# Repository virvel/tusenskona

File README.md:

# tusenskona

Breakout board for Daisy Seed

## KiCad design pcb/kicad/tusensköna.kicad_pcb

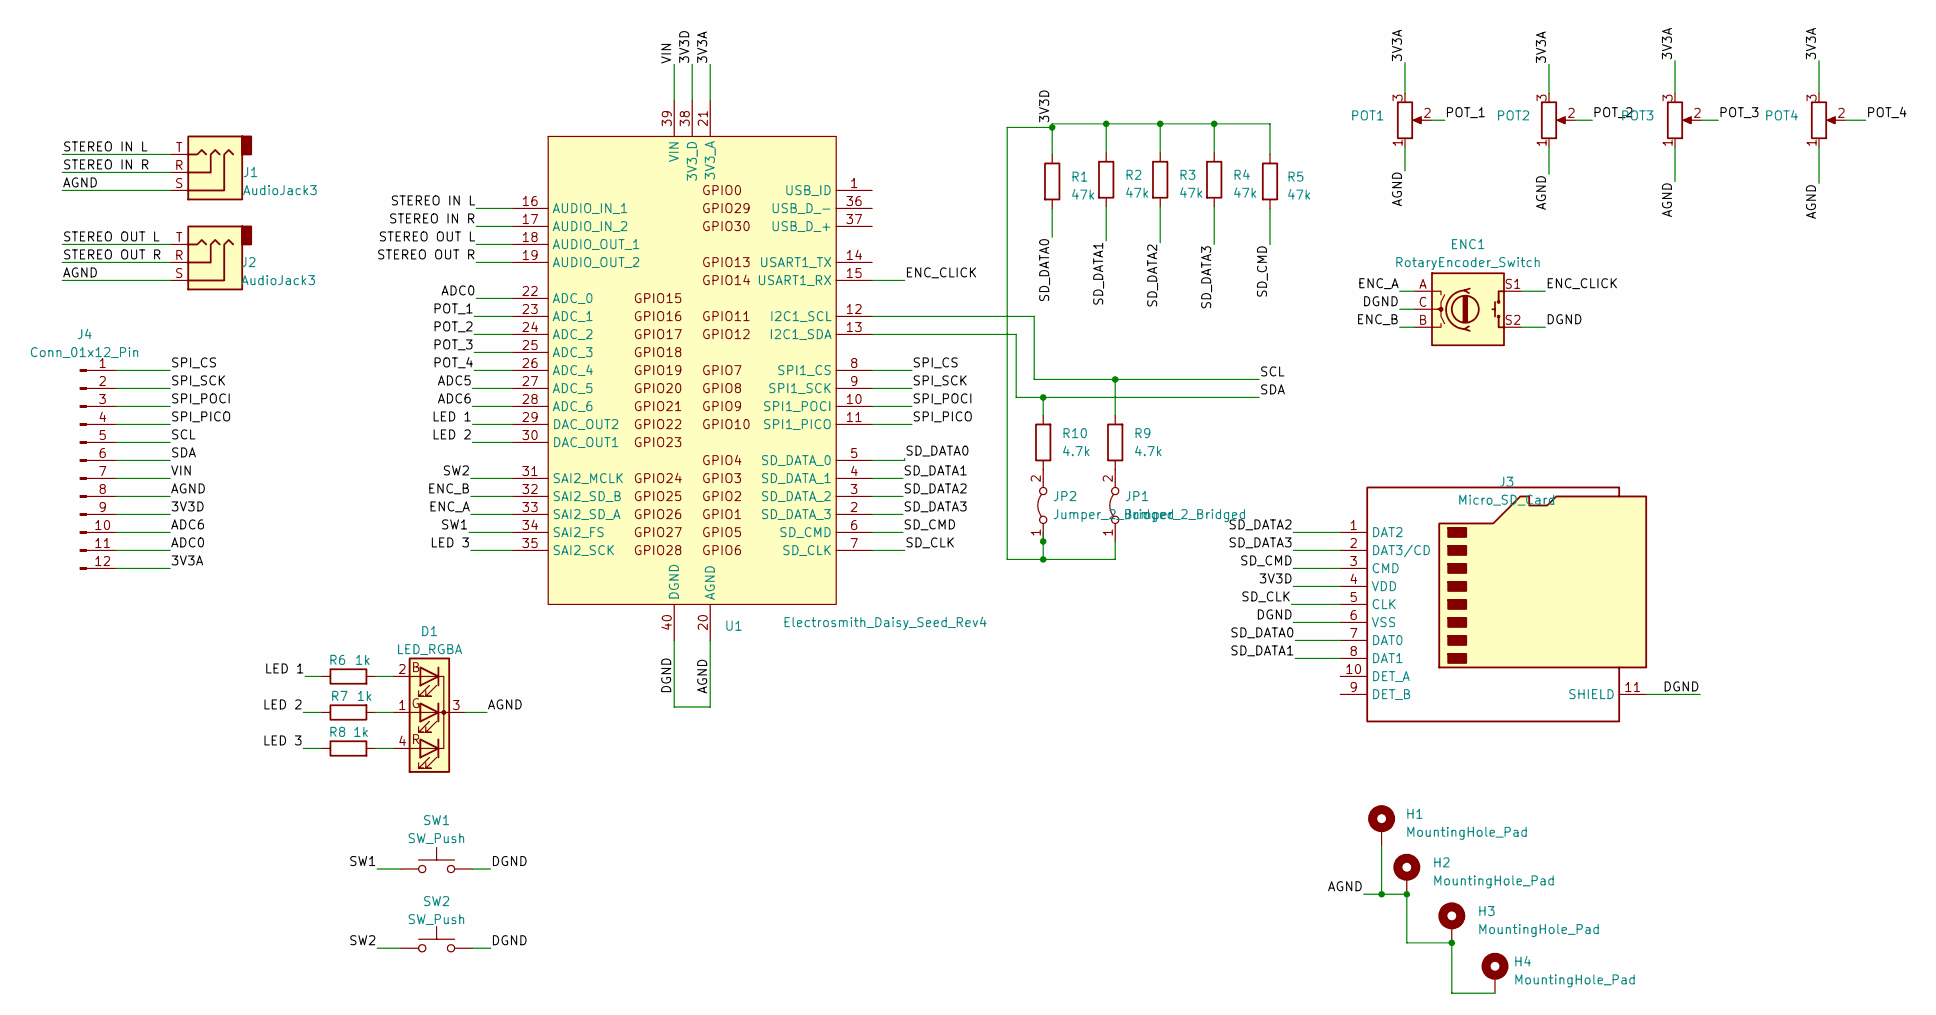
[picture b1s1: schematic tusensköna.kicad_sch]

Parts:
D1: LED_RGBA; LED_D5.0mm-4_RGB
ENC1: RotaryEncoder_Switch; RotaryEncoder_Bourns_Vertical_PEC12R-3xxxF-Sxxxx
H1, H2, H3, H4: MountingHole_Pad; MountingHole_3.2mm_M3_Pad
J1, J2: AudioJack3; Jack_3.5mm_CUI_SJ1-3533NG_Horizontal_CircularHoles
J3: Micro_SD_Card; microSD_HC_Hirose_DM3D-SF
J4: Conn_01x12_Pin; PinHeader_1x12_P2.54mm_Vertical
JP1, JP2: Jumper_2_Bridged; PinHeader_1x02_P2.54mm_Vertical
POT1, POT2, POT3, POT4: R_Potentiometer; Potentiometer_Alps_RK09K_Single_Vertical
R1, R2, R3, R4, R5: 47k; R_0805_2012Metric
R6, R7, R8: 1k; R_0805_2012Metric
R9, R10: 4.7k; R_0805_2012Metric
SW1, SW2: SW_Push; SW_PUSH_6mm
U1: Electrosmith_Daisy_Seed_Rev4; Electrosmith_Daisy_Seed

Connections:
/3V3A: J4.12, POT1.3, POT2.3, POT3.3, POT4.3, U1.21 (3V3_A)
/3V3D: J3.4 (VDD), J4.9, JP1.1 (A), JP2.1 (A), R1.1, R2.1, R3.1, R4.1, R5.1, U1.38 (3V3_D)
/ADC0: J4.11, U1.22 (ADC_0)
/ADC5: U1.27 (ADC_5)
/ADC6: J4.10, U1.28 (ADC_6)
/AGND: D1.3 (K), ENC1.C, ENC1.S2, H1.1, H2.1, H3.1, H4.1, J1.S, J2.S, J3.6 (VSS), J3.11 (SHIELD), J4.8, POT1.1, POT2.1, POT3.1, POT4.1, SW1.2, SW2.2, U1.20 (AGND), U1.40 (DGND)
/ENC_A: ENC1.A, U1.33 (SAI2_SD_A)
/ENC_B: ENC1.B, U1.32 (SAI2_SD_B)
/ENC_CLICK: ENC1.S1, U1.15 (USART1_RX)
/I2C_SCL: J4.5, R9.2, U1.12 (I2C1_SCL)
/I2C_SDA: J4.6, R10.2, U1.13 (I2C1_SDA)
/LED 1: R6.1, U1.29 (DAC_OUT2)
/LED 2: R7.1, U1.30 (DAC_OUT1)
/LED 3: R8.1, U1.35 (SAI2_SCK)
/POT_1: POT1.2, U1.23 (ADC_1)
/POT_2: POT2.2, U1.24 (ADC_2)
/POT_3: POT3.2, U1.25 (ADC_3)
/POT_4: POT4.2, U1.26 (ADC_4)
/SD_CLK: J3.5 (CLK), U1.7 (SD_CLK)
/SD_CMD: J3.3 (CMD), R5.2, U1.6 (SD_CMD)
/SD_DATA0: J3.7 (DAT0), R1.2, U1.5 (SD_DATA_0)
/SD_DATA1: J3.8 (DAT1), R2.2, U1.4 (SD_DATA_1)
/SD_DATA2: J3.1 (DAT2), R3.2, U1.3 (SD_DATA_2)
/SD_DATA3: J3.2 (DAT3/CD), R4.2, U1.2 (SD_DATA_3)
/SPI_CS: J4.1, U1.8 (SPI1_CS)
/SPI_PICO: J4.4, U1.11 (SPI1_PICO)
/SPI_POCI: J4.3, U1.10 (SPI1_POCI)
/SPI_SCK: J4.2, U1.9 (SPI1_SCK)
/STEREO IN L: J1.T, U1.16 (AUDIO_IN_1)
/STEREO IN R: J1.R, U1.17 (AUDIO_IN_2)
/STEREO OUT L: J2.T, U1.18 (AUDIO_OUT_1)
/STEREO OUT R: J2.R, U1.19 (AUDIO_OUT_2)
/SW1: SW1.1, U1.34 (SAI2_FS)
/SW2: SW2.1, U1.31 (SAI2_MCLK)
/VIN: J4.7, U1.39 (VIN)
unnamed: D1.2 (BA), R6.2
unnamed: D1.1 (GA), R7.2
unnamed: D1.4 (RA), R8.2
unnamed: JP1.2 (B), R9.1
unnamed: JP2.2 (B), R10.1

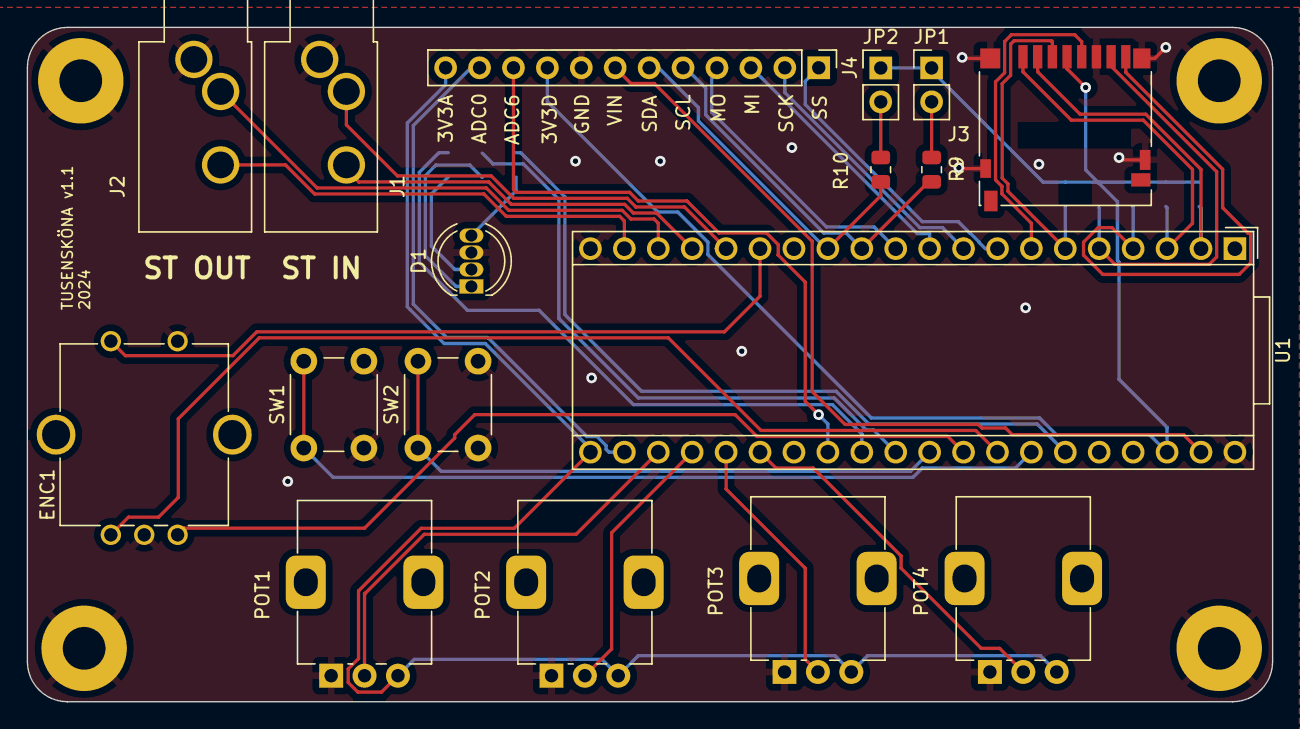
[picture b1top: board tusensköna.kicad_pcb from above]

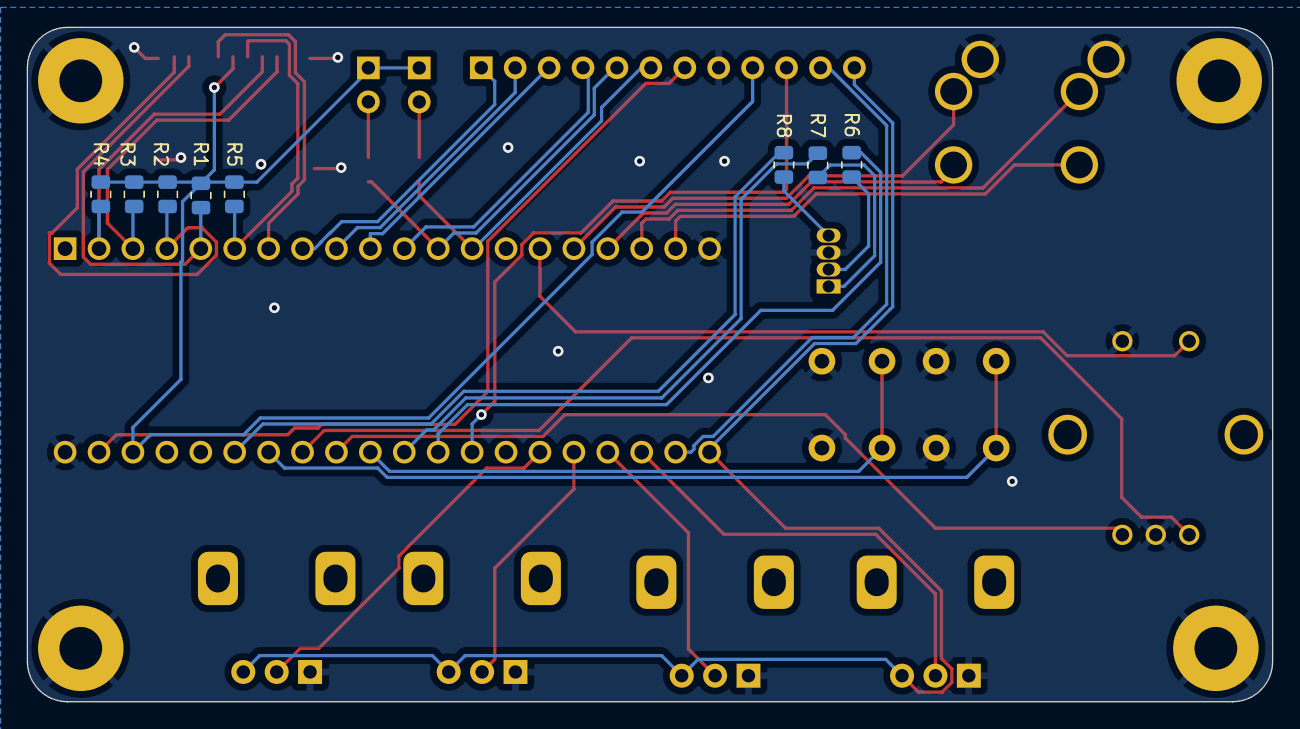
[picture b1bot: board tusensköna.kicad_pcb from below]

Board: 2 copper layers, 93.2 x 50.5 mm, 29 parts (8 on the bottom side), 39 nets.

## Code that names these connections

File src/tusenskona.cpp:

#include "tusenskona.h"

#ifndef SAMPLE_RATE
//#define SAMPLE_RATE DSY_AUDIO_SAMPLE_RATE
#define SAMPLE_RATE 48014.f
#endif


#define SW_1_PIN 27
#define SW_2_PIN 24

#define ENC_A_PIN 26
#define ENC_B_PIN 25
#define ENC_CLICK_PIN 14

#define LED_R_PIN 28
#define LED_G_PIN 23
#define LED_B_PIN 22

#define KNOB_1_PIN 16
#define KNOB_2_PIN 17
#define KNOB_3_PIN 18
#define KNOB_4_PIN 19

using namespace daisy;

void Tusenskona::Init(bool boost)
{
    seed.Configure();
    seed.Init(boost);
    InitButtons();
    InitEncoder();
    InitLeds();
    InitKnobs();
    SetAudioBlockSize(48);
}

void Tusenskona::DelayMs(size_t del)
{
    seed.DelayMs(del);
}


void Tusenskona::SetHidUpdateRates()
{
    for(int i = 0; i < KNOB_LAST; i++)
    {
        knobs[i]->SetSampleRate(AudioCallbackRate());
    }
}

void Tusenskona::StartAudio(AudioHandle::InterleavingAudioCallback cb)
{
    seed.StartAudio(cb);
}

void Tusenskona::StartAudio(AudioHandle::AudioCallback cb)
{
    seed.StartAudio(cb);
}

void Tusenskona::ChangeAudioCallback(AudioHandle::InterleavingAudioCallback cb)
{
    seed.ChangeAudioCallback(cb);
}

void Tusenskona::ChangeAudioCallback(AudioHandle::AudioCallback cb)
{
    seed.ChangeAudioCallback(cb);
}

void Tusenskona::StopAudio()
{
    seed.StopAudio();
}

void Tusenskona::SetAudioBlockSize(size_t size)
{
    seed.SetAudioBlockSize(size);
    SetHidUpdateRates();
}

size_t Tusenskona::AudioBlockSize()
{
    return seed.AudioBlockSize();
}

void Tusenskona::SetAudioSampleRate(SaiHandle::Config::SampleRate samplerate)
{
    seed.SetAudioSampleRate(samplerate);
    SetHidUpdateRates();
}

float Tusenskona::AudioSampleRate()
{
    return seed.AudioSampleRate();
}

float Tusenskona::AudioCallbackRate()
{
    return seed.AudioCallbackRate();
}

void Tusenskona::StartAdc()
{
    seed.adc.Start();
}

void Tusenskona::StopAdc()
{
    seed.adc.Stop();
}


void Tusenskona::ProcessAnalogControls()
{
    knob1.Process();
    knob2.Process();
    knob3.Process();
    knob4.Process();
}

float Tusenskona::GetKnobValue(Knob k)
{
    size_t idx;
    idx = k < KNOB_LAST ? k : KNOB_1;
    return knobs[idx]->Value();
}

void Tusenskona::ProcessDigitalControls()
{
    encoder.Debounce();
    button1.Debounce();
    button2.Debounce();
}

void Tusenskona::ClearLeds()
{
    led.Set(0.0f, 0.0f, 0.0f);
}

void Tusenskona::UpdateLeds()
{
    led.Update();
}

void Tusenskona::InitButtons()
{
    // button1
    button1.Init(seed.GetPin(SW_1_PIN));
    // button2
    button2.Init(seed.GetPin(SW_2_PIN));

    buttons[BUTTON_1] = &button1;
    buttons[BUTTON_2] = &button2;
}

void Tusenskona::InitEncoder()
{
    dsy_gpio_pin a, b, click;
    a     = seed.GetPin(ENC_A_PIN);
    b     = seed.GetPin(ENC_B_PIN);
    click = seed.GetPin(ENC_CLICK_PIN);
    encoder.Init(a, b, click);
}

void Tusenskona::InitLeds()
{
    dsy_gpio_pin rpin, gpin, bpin;

    rpin = seed.GetPin(LED_R_PIN);
    gpin = seed.GetPin(LED_G_PIN);
    bpin = seed.GetPin(LED_B_PIN);
    led.Init(rpin, gpin, bpin, false);

    ClearLeds();
    UpdateLeds();
}
void Tusenskona::InitKnobs()
{
    // Configure the ADC channels using the desired pin
    AdcChannelConfig knob_init[KNOB_LAST];
    knob_init[KNOB_1].InitSingle(seed.GetPin(KNOB_1_PIN));
    knob_init[KNOB_2].InitSingle(seed.GetPin(KNOB_2_PIN));
    knob_init[KNOB_3].InitSingle(seed.GetPin(KNOB_3_PIN));
    knob_init[KNOB_4].InitSingle(seed.GetPin(KNOB_4_PIN));
    // Initialize with the knob init struct w/ 2 members
    // Set Oversampling to 32x
    seed.adc.Init(knob_init, KNOB_LAST);
    // Make an array of pointers to the knobs.
    knobs[KNOB_1] = &knob1;
    knobs[KNOB_2] = &knob2;
    knobs[KNOB_3] = &knob3;
    knobs[KNOB_4] = &knob4;
    for(int i = 0; i < KNOB_LAST; i++)
    {
        knobs[i]->Init(seed.adc.GetPtr(i), seed.AudioCallbackRate());
    }
}

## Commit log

2023-06-21 firstest
2023-06-21 added pcb
2023-06-21 added image
2023-06-22 moved stuff
2023-06-22 fixed LEDs in cpp test
2023-06-22 removed junk
2023-06-25 added chebyshev example
2023-10-25 Create LICENSE
2023-11-12 added granular example
2023-11-12 fixed pots and readme
2023-11-12 fixed readme ffor granulator
2023-11-30 cleanup
2024-03-09 added kicad files
2024-03-09 issues fixed
2024-03-09 purge and fix
2024-03-09 pullup
2024-03-10 fixed gnd planes and cleanup
2024-03-10 stereo connectors outside of the board
2024-03-10 removed temp junk
2024-03-10 fixed ground plane
2024-03-11 schematic and gnd plane
    Fixed errors where connection to gnd plane was insufficient for some components.
    Moved some components to make space for heat dissipation.
    Cleaned up part of schematic regarding pullup resistors.
2024-04-01 trillhandler and gitmodules pointing to modified libDaisy
2024-04-03 float cmp
2024-04-03 added vsandstrom dspheaders
2024-04-03 dsp-headers added as dependency
2024-04-03 modified paths
2024-04-03 paths working
2024-04-03 fix paths
2024-04-03 removed trill from grainstrom
2024-04-04 trill handler working
2024-04-04 local paths
2024-04-04 updated submodules
2024-04-04 updated virveldsp
2024-04-04 removed use of daisysp LGPL classes
2024-04-04 fixed readme
